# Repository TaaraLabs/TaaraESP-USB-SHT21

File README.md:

TaaraESP SHT21 USB
==================

TaaraESP SHT21 USB Wifi Temperature and Humidity sensor

[WebSite](https://taaralabs.eu/es4)

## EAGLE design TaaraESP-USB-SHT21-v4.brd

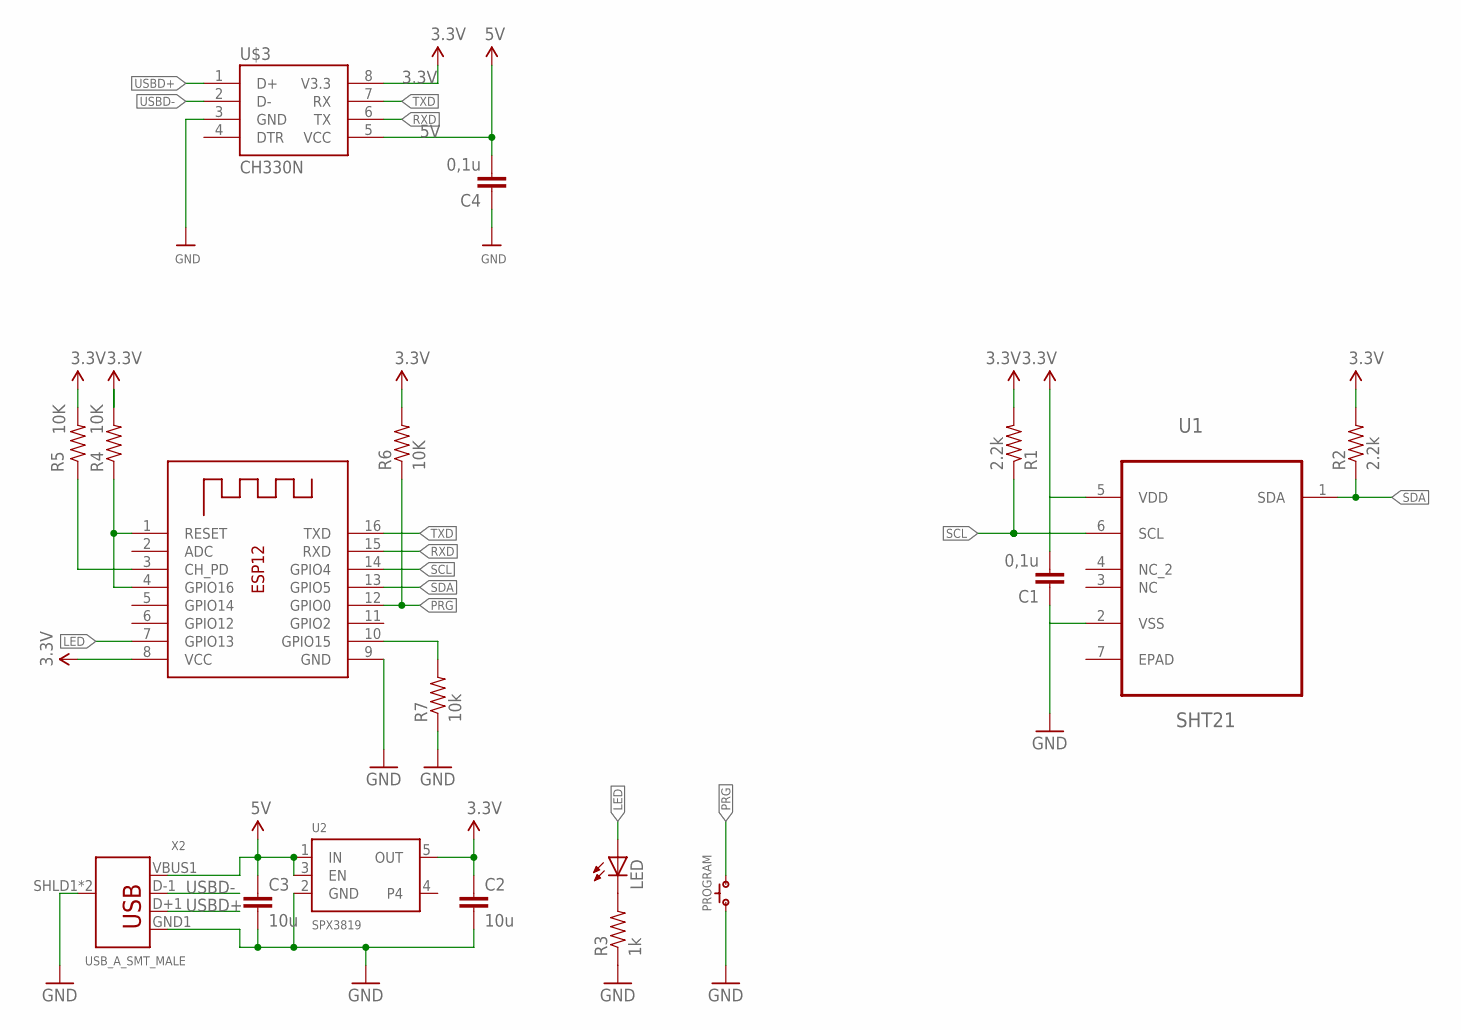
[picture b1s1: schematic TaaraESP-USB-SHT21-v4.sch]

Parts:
C1, C4: 0,1u; 0805
C2, C3: 10u; 0805
LED: LEDCHIPLED_0603; CHIPLED_0603
PROGRAM: SPST.B3U-1000P(M)-B; B3U-1000P(M)-B
R1, R2: 2.2k; 0805
R3: 1k; 0805
R4, R5, R6: 10K; 0805
R7: 10k; 0805
U1: SHT21; DFN300X300X110-7N
U2: SPX3819; SOT23-5
U$3: CH330N; SOIC8
X1: ESP-12S; ESP-12
X2: USB_A_SMT_MALE; USB-A-SMT-MALE

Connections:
3.3V: C1.2, C2.1, R1.2, R2.2, R4.2, R5.2, R6.2, U1.5 (VDD), U2.5 (OUT), U$3.8 (V3.3), X1.8 (VCC)
5V: C3.1, C4.2, U2.1 (IN), U2.3 (EN), U$3.5 (VCC), X2.VBUS1 (VBUS)
DTR: U$3.4 (DTR)
GND: C1.1, C2.2, C3.2, C4.1, PROGRAM.1, R3.1, R7.1, U1.2 (VSS), U2.2 (GND), U$3.3 (GND), X1.9 (GND), X2.GND1 (GND), X2.SHLD1 (SHIELD), X2.SHLD2 (SHIELD)
LED: LED.A, X1.7 (GPIO13)
unnamed: LED.C, R3.2
unnamed: R4.1, X1.1 (RESET), X1.4 (GPIO16)
unnamed: R5.1, X1.3 (CH_PD)
unnamed: R7.2, X1.10 (GPIO15)
PRG: PROGRAM.2, R6.1, X1.12 (GPIO0)
RXD: U$3.6 (TX), X1.15 (RXD)
SCL: R1.1, U1.6 (SCL), X1.14 (GPIO4)
SDA: R2.1, U1.1 (SDA), X1.13 (GPIO5)
TXD: U$3.7 (RX), X1.16 (TXD)
USBD+: U$3.1 (D+), X2.D+1 (D+)
USBD-: U$3.2 (D-), X2.D-1 (D-)

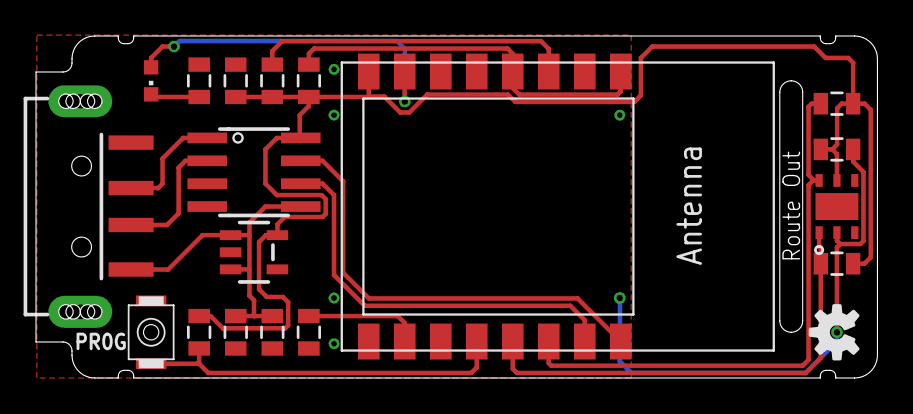
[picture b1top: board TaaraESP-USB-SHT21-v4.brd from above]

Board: 2 copper layers, 46.7 x 19.0 mm, 20 parts (1 on the bottom side), 15 nets.

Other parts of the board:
U$1, U$5: OSHW-LOGO-S

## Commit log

2021-08-21 i2c default pins

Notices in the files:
parts and their libraries:
microbuilder: This work is placed in the public domain, and may be freely used for commercial and non-commercial work with the following conditions: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
SparkFun-Aesthetics: Licensing: CC v3.0 Share-Alike You are welcome to use this library for commercial purposes.
